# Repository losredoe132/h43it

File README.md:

# H43it 
A minimialistic habit tracker to assist you by create a lifestyle full of good habits. 

## Dev Setup 
### Python Environment
1. Create a virtual environment in order to be able to excecute the python scripts: 
`python3 -m venv .venv` 
2. Activate it: `.\.venv\Scripts\activate` (powershell on Windows) `source ./.venv/bin/activate` (linux shell). 
3. Install the required python packages: `pip install -r requirements.txt `. 

Not you are good to go!

## Finite State Machine (FSM)
The implementation is done as FSM. You can take a look at [this graph visu](FSM.html) to get an overview. Connection to serial port is only possible in Edge and Chrome browsers.

## How to use 
1. Define the FSM in the [state_machine_translator.py](software\tools\state_machine_translator.py)
2. Execute state_maschine_translator.py to get the `FSM.html` and the `transition_table.c`. 
3. You have to define the used transition conditions in `transition_conditions.c`. 
4. Build and flash the code to the board

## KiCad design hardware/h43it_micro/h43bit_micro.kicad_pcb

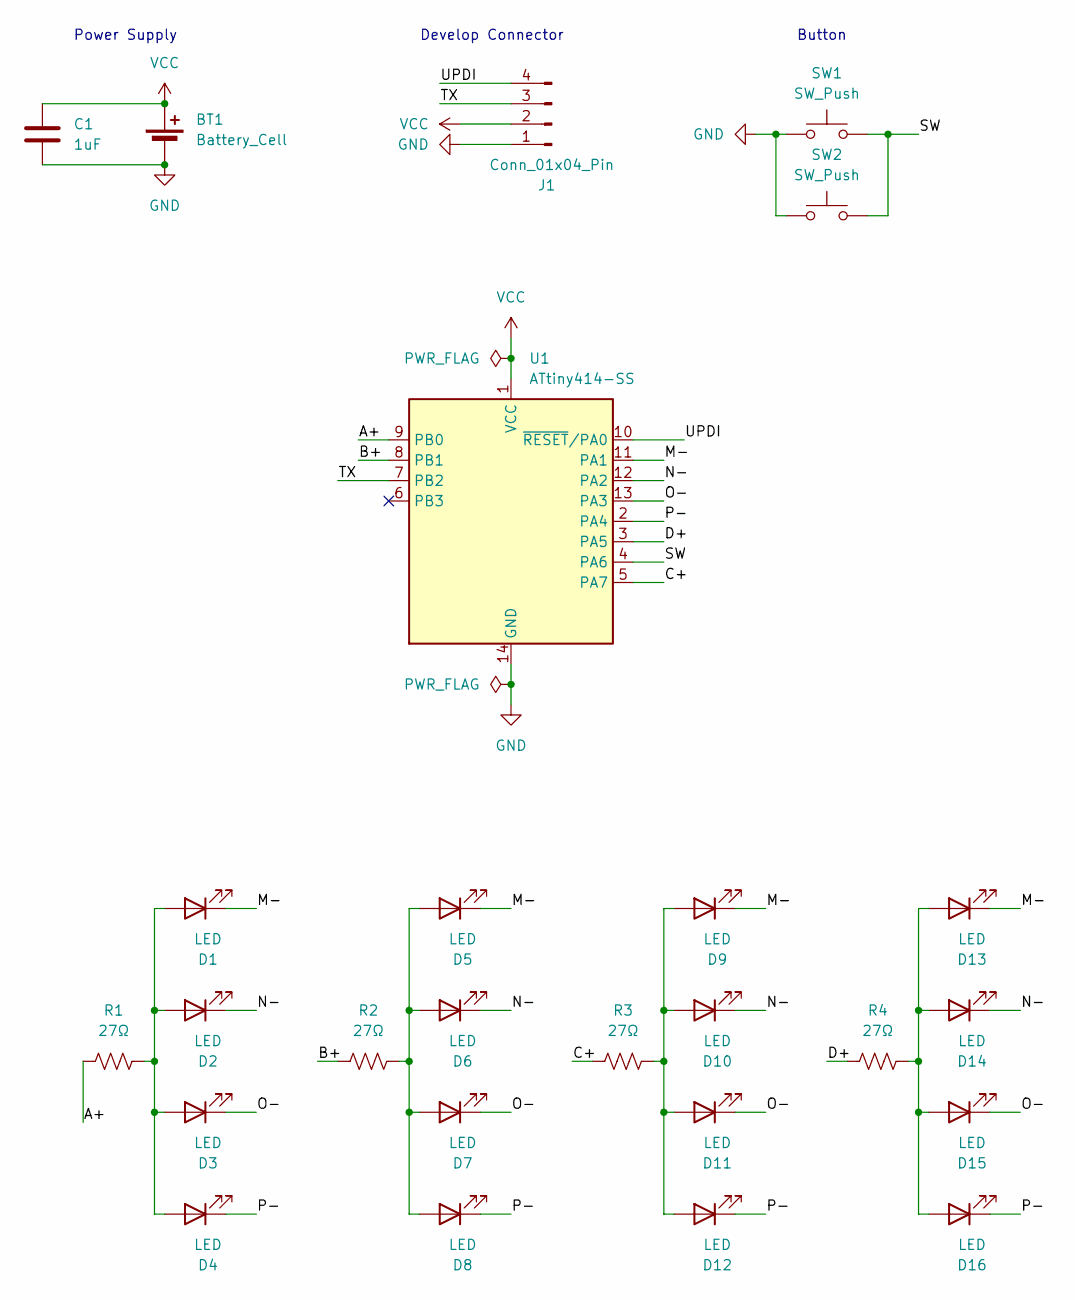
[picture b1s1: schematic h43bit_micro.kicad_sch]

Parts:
BT1: Battery_Cell; BAT-HLD-001
C1: 1uF; C_0805_2012Metric
D1, D2, D3, D4, D5, D6, D7, D8, D9, D10, D11, D12, D13, D14, D15, D16: LED; LED_0805_2012Metric
J1: Conn_01x04_Pin; PinHeader_1x04_P2.54mm_Vertical
R1, R2, R3, R4: 27Ω; R_0805_2012Metric
SW1: SW_Push; PTS526 SM15 SMTR2 LFS
SW2: SW_Push; FSM2JSMAATR
U1: ATtiny414-SS; SOIC-14_3.9x8.7mm_P1.27mm

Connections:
/A+: R1.1, U1.9 (PB0)
/B+: R2.1, U1.8 (PB1)
/C+: R3.1, U1.5 (PA7)
/D+: R4.1, U1.3 (PA5)
/M-: D1.1 (K), D5.1 (K), D9.1 (K), D13.1 (K), U1.11 (PA1)
/N-: D2.1 (K), D6.1 (K), D10.1 (K), D14.1 (K), U1.12 (PA2)
/O-: D3.1 (K), D7.1 (K), D11.1 (K), D15.1 (K), U1.13 (PA3)
/P-: D4.1 (K), D8.1 (K), D12.1 (K), D16.1 (K), U1.2 (PA4)
/SW: SW1.2, SW2.2, U1.4 (PA6)
/TX: J1.3, U1.7 (PB2)
/UPDI: J1.4, U1.10 (~RESET/PA0)
GND: BT1.2 (-), C1.2, J1.1, SW1.1, SW2.1, U1.14 (GND)
unnamed: D1.2 (A), D2.2 (A), D3.2 (A), D4.2 (A), R1.2
unnamed: D5.2 (A), D6.2 (A), D7.2 (A), D8.2 (A), R2.2
unnamed: D9.2 (A), D10.2 (A), D11.2 (A), D12.2 (A), R3.2
unnamed: D13.2 (A), D14.2 (A), D15.2 (A), D16.2 (A), R4.2
VCC: BT1.1 (+), C1.1, J1.2, U1.1 (VCC)

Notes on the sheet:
Develop Connector
Power Supply
Button

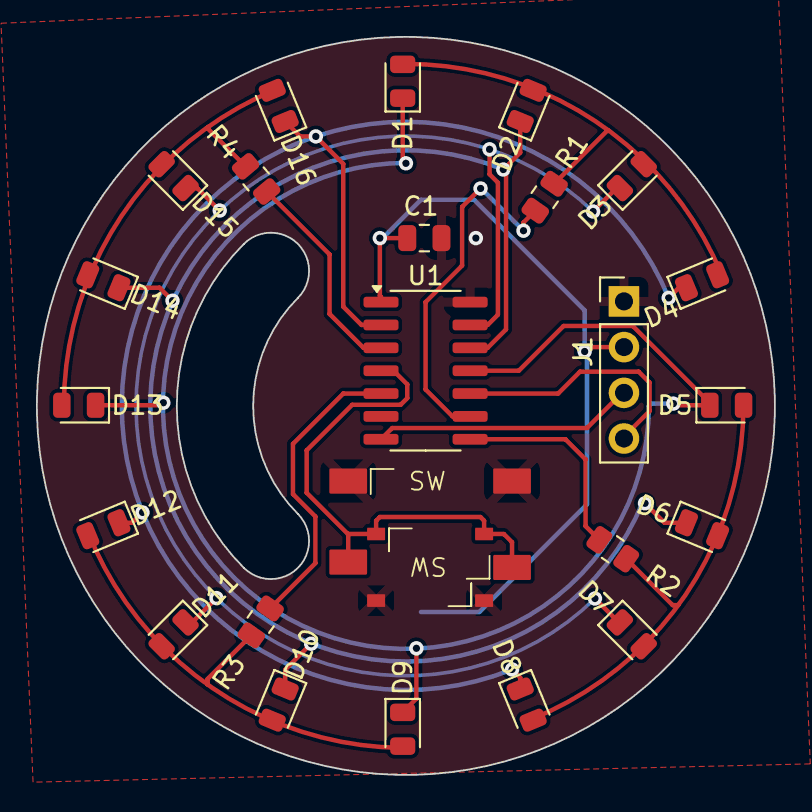
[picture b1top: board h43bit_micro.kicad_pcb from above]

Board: 2 copper layers, 41.0 x 41.0 mm, 26 parts (1 on the bottom side), 17 nets.

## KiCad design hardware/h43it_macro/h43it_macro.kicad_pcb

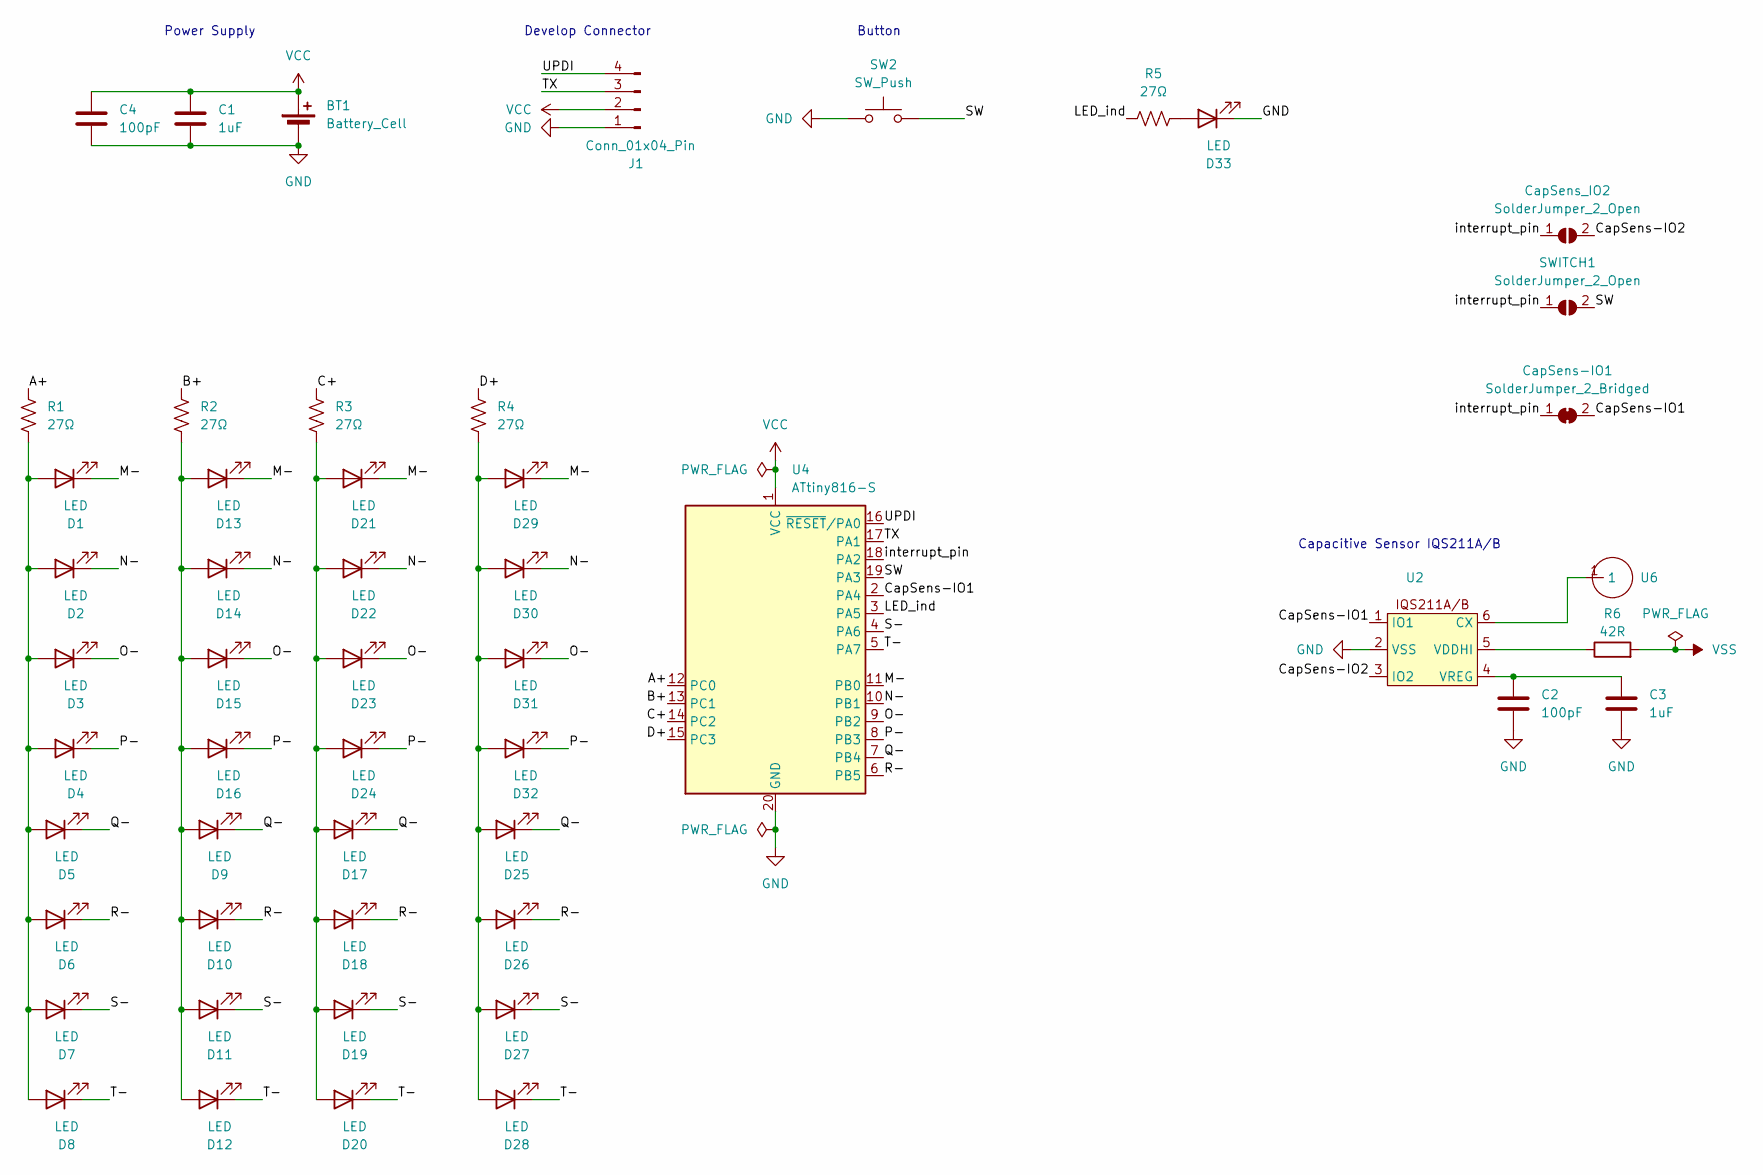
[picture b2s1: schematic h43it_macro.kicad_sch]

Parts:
BT1: Battery_Cell; Battery_holder__Keystone_Electronic_AA_2462
C1, C3: 1uF; C_0805_2012Metric
C2, C4: 100pF; C_0805_2012Metric
CapSens-IO1: SolderJumper_2_Bridged; SolderJumper-2_P1.3mm_Bridged_RoundedPad1.0x1.5mm
CapSens_IO2: SolderJumper_2_Open; SolderJumper-2_P1.3mm_Open_RoundedPad1.0x1.5mm
D1, D2, D3, D4, D5, D6, D7, D8, D9, D10, D11, D12, D13, D14, D15, D16, D17, D18, D19, D20, D21, D22, D23, D24, D25, D26, D27, D28, D29, D30, D31, D32, D33: LED; LED_0805_2012Metric
J1: Conn_01x04_Pin; PinHeader_1x04_P2.54mm_Vertical
R1, R2, R3, R4, R5: 27Ω; R_0805_2012Metric
R6: 42R; R_0805_2012Metric
SW2: SW_Push; FSM2JSMAATR
SWITCH1: SolderJumper_2_Open; SolderJumper-2_P1.3mm_Open_RoundedPad1.0x1.5mm
U2: TSOT32-6
U4: ATtiny816-S; SOIC-20W_7.5x12.8mm_P1.27mm
U6: TouchButton-15x10mm

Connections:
/A+: R1.2, U4.12 (PC0)
/B+: R2.2, U4.13 (PC1)
/C+: R3.2, U4.14 (PC2)
/CapSens-IO1: CapSens-IO1.2 (B), U2.1 (IO1), U4.2 (PA4)
/CapSens-IO2: CapSens_IO2.2 (B), U2.3 (IO2)
/D+: R4.2, U4.15 (PC3)
/LED_ind: R5.2, U4.3 (PA5)
/M-: D1.1 (K), D13.1 (K), D21.1 (K), D29.1 (K), U4.11 (PB0)
/N-: D2.1 (K), D14.1 (K), D22.1 (K), D30.1 (K), U4.10 (PB1)
/O-: D3.1 (K), D15.1 (K), D23.1 (K), D31.1 (K), U4.9 (PB2)
/P-: D4.1 (K), D16.1 (K), D24.1 (K), D32.1 (K), U4.8 (PB3)
/Q-: D5.1 (K), D9.1 (K), D17.1 (K), D25.1 (K), U4.7 (PB4)
/R-: D6.1 (K), D10.1 (K), D18.1 (K), D26.1 (K), U4.6 (PB5)
/S-: D7.1 (K), D11.1 (K), D19.1 (K), D27.1 (K), U4.4 (PA6)
/SW: SW2.2, SWITCH1.2 (B), U4.19 (PA3)
/T-: D8.1 (K), D12.1 (K), D20.1 (K), D28.1 (K), U4.5 (PA7)
/TX: J1.3, U4.17 (PA1)
/UPDI: J1.4, U4.16 (~RESET/PA0)
/interrupt_pin: CapSens-IO1.1 (A), CapSens_IO2.1 (A), SWITCH1.1 (A), U4.18 (PA2)
GND: BT1.2 (-), C1.2, C2.2, C3.2, C4.2, D33.1 (K), J1.1, SW2.1, U2.2 (VSS), U4.20 (GND)
unnamed: D1.2 (A), D2.2 (A), D3.2 (A), D4.2 (A), D5.2 (A), D6.2 (A), D7.2 (A), D8.2 (A), R1.1
unnamed: D9.2 (A), D10.2 (A), D11.2 (A), D12.2 (A), D13.2 (A), D14.2 (A), D15.2 (A), D16.2 (A), R2.1
unnamed: D17.2 (A), D18.2 (A), D19.2 (A), D20.2 (A), D21.2 (A), D22.2 (A), D23.2 (A), D24.2 (A), R3.1
unnamed: D25.2 (A), D26.2 (A), D27.2 (A), D28.2 (A), D29.2 (A), D30.2 (A), D31.2 (A), D32.2 (A), R4.1
unnamed: D33.2 (A), R5.1
unnamed: U2.6 (CX), U6.1
unnamed: R6.1, U2.5 (VDDHI)
unnamed: C2.1, C3.1, U2.4 (VREG)
VCC: BT1.1 (+), C1.1, C4.1, J1.2, U4.1 (VCC)
VSS: R6.2

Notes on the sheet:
Button
Power Supply
Capacitive Sensor IQS211A/B
Develop Connector

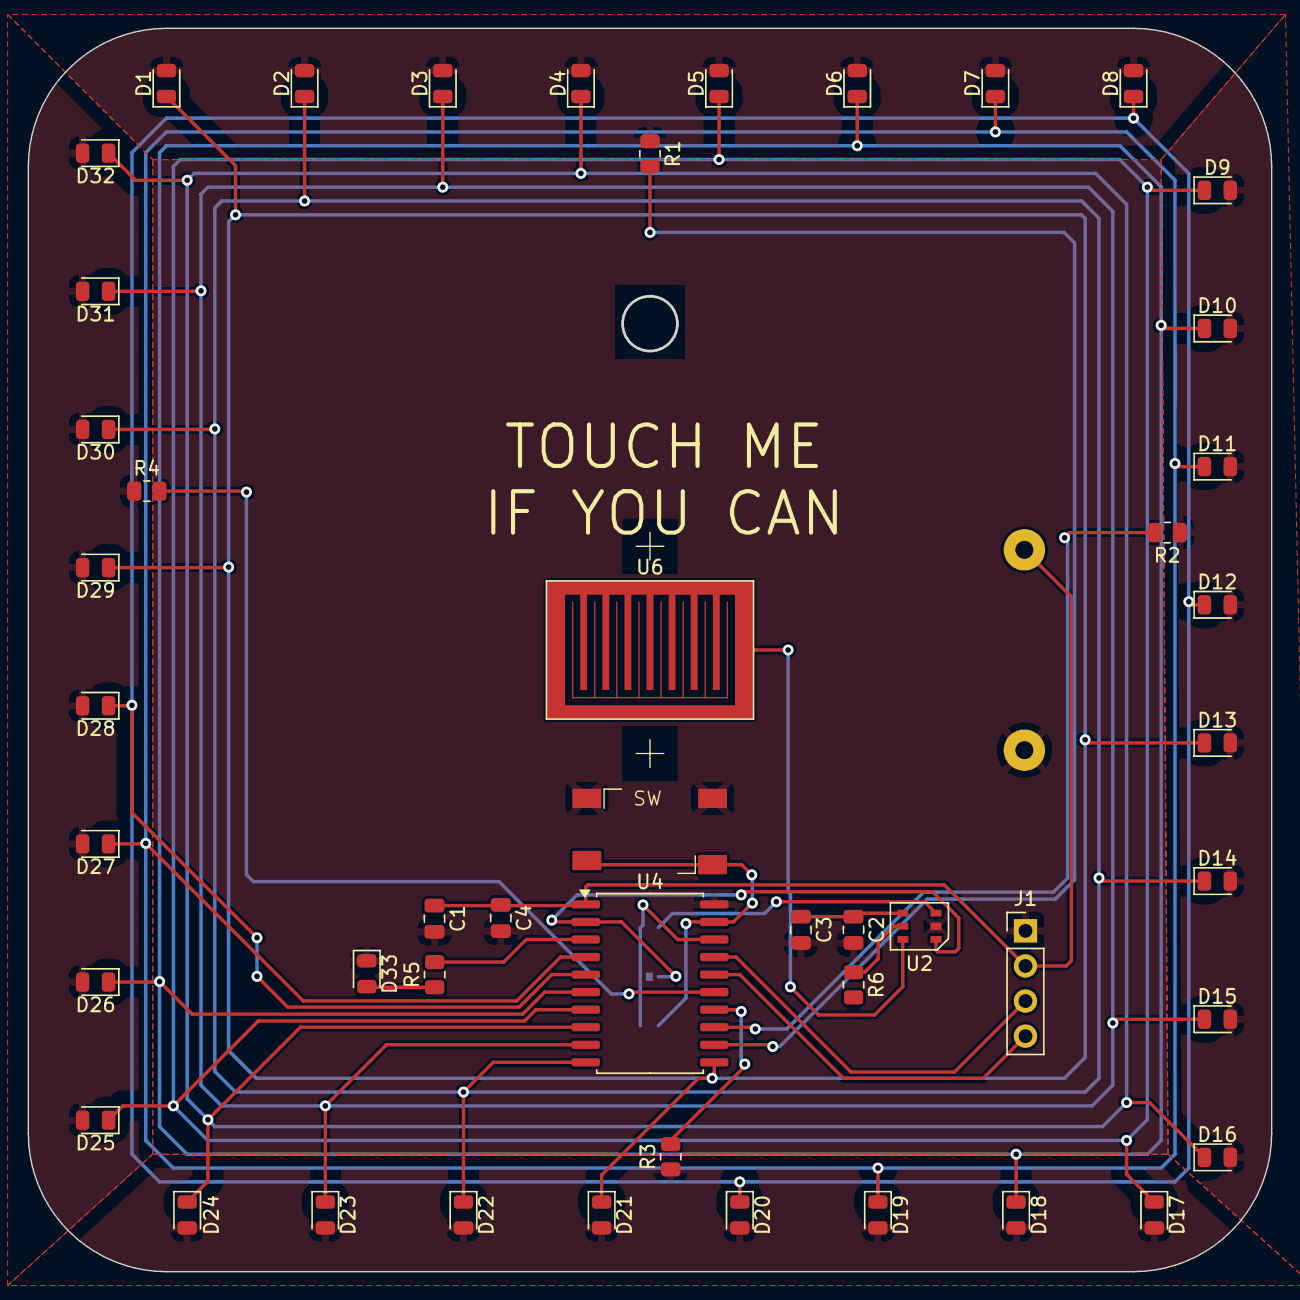
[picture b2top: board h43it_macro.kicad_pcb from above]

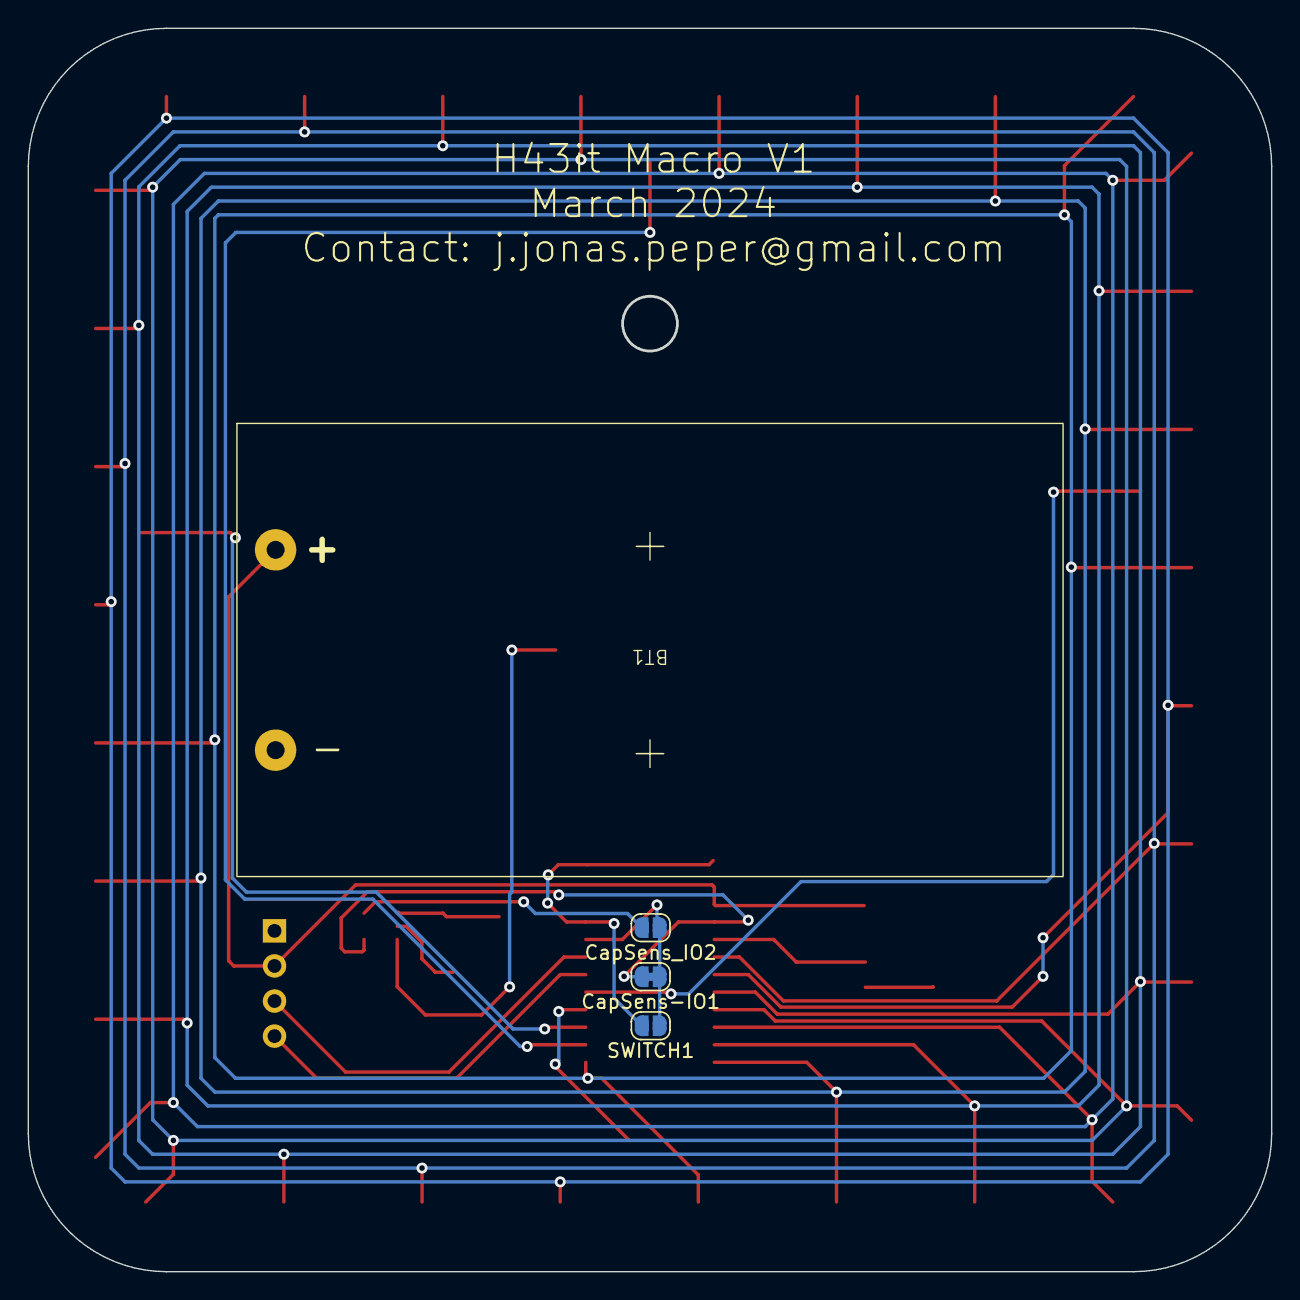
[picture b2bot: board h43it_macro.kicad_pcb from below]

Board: 2 copper layers, 89.9 x 89.9 mm, 52 parts (4 on the bottom side), 29 nets.

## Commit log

2024-02-11 intial
2024-02-14 working printf command
2024-02-14 add delay
2024-02-17 working button and led
2024-02-24 working blink with for loop
2024-02-24 all LEDs working in double for loop
2024-02-24 2d array for all leds
2024-02-24 working button
2024-02-26 working button example
2024-02-27 working isr counting up
2024-02-27 working RTC timer
2024-02-27 using timer and pin interrupt in parallel
2024-02-28 wokring debounce
2024-02-28 working sleep
2024-02-28 working peripdic awakening but only in idle not power down
2024-02-29 fixed last brightest bug
2024-02-29 working PIT with POWER DOWN
2024-02-29 1st mvp
2024-03-01 TCA and TCB working together
2024-03-01 TCA and TCB working together - part 2
2024-03-01 increasing by long button press
2024-03-01 oing to sleep after inactivity but never wake up again
2024-03-02 annis gift state
2024-03-02 working sleep and robust button commands
2024-03-02 working sleep and robust button command even with PWR DOWN
2024-03-02 fix dont want to go to sleep bug
2024-03-02 user has to click once to wake up and only then it is possible to increase
2024-03-02 working reset and forbiden increase
2024-03-04 annis adaptions
2024-03-09 resturcture and add gitignore for hardware and software dev
2024-03-09 remove unneeded folder
2024-03-09 add README
2024-03-09 first draft of schematic
2024-03-09 draft of a circular micro
2024-03-10 circular tracks
2024-03-11 changes transfer
2024-03-11 filled area
2024-03-11 fill with smaller clearence to incorperate all areas at top
2024-03-12 first draft of a finished pcb
2024-03-13 add macro pcb project
2024-03-13 schematic draft finsihed
2024-03-18 add twin attiny 816
2024-03-24 pcb for macro
2024-03-24 pcb for macro 2
2024-03-24 pcb for macro 3
2024-03-24 pcb for macro 4
2024-03-26 tiny changes and added R6
2024-03-28 switch SW on micro
2024-03-28 no errors in macro
2024-03-28 no errors in micro
2024-03-28 recreate production files
2024-03-31 success all DRC
2024-04-11 working micro
2024-04-11 split software in mico and macro
2024-04-12 add macro code
2024-04-13 working macro
2024-07-04 FSM_schema.drawio eingefügt
2024-07-25 alternative usart on h43it macro
2024-07-25 update repo according to gitignore
2024-07-25 restructure source code in seperate files
2024-07-26 minimal FSM
2024-07-26 first FSM working with transition conditions as function pointers
2024-07-26 fully functional 2 state FSM with button as condition
2024-07-26 tiny led 2 state demo
2024-07-26 html visu for FSM
2024-07-27 working FSM generation from json in python including html generation
2024-07-27 transition with condition, wokring scaling in html visu
2024-07-27 add FSM HTML and README
2024-07-27 working code generation in general
2024-07-27 working FSM code generation
2024-07-27 working FSM code generation - with some bugfixes
2024-07-27 clean up FSM example definition
2024-07-27 working FSM visualisation in HTMl based on auto generated code
2024-07-27 working button conditions
2024-07-27 more complex example
2024-07-27 more complex example - addtional node
2024-07-28 sorting of function names
2024-07-28 add requirements.txt and setup instructions
2024-07-28 clean up and add encoding for file saving
2024-07-28 working going to sleep
2024-07-28 adding Serial output to html
2024-07-28 working sleep with wake up on button
2024-07-28 working prototype macro
2024-07-28 time counting only in PIT wirhout missedActivation state
2024-07-28 added daycounter to prevent overflow and set newday to 24h
2024-07-28 format all c++ code
2024-07-28 working daycounter visu
2024-07-29 update today indication
2024-07-29 change to 24h and change init with first day already activated
2024-08-01 get status led running
2024-08-01 added init state to check leds are working after power up
